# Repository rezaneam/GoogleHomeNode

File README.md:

# Smart IoT Sensor - Lite Version of [sAmbiente](https://github.com/rezaneam/sAmbiente)

This project introduces proof of concept for a Smart Home Device/Sensor/Monitoring with a different approach.
In this project, Bosch & TI environment sensors (BMP280, BME280, BME680, HDC1080) were utilized to monitor the temperature, humidity, pressure, and air quality.

## What is innovative in this project

- The configuration process of the Smart IoT Sensor is straightforward and you can update it at anytime.
- The Sensor pushes real-time readings via BluetoothLE to multiple connected devices.
- Against many available solutions, you don't need to open a port in your router/modem/firewall. That's really cumbersome and may be secuirty issues.
- You don't need to deal with DNS and static IP address. that's a real pain.
- You don't need to register on expensive and complicated services (Azure IoT Hub service has a free plan).
- You can customize the whole project with a little effort.

## Components

This project includes the following components

- ESP32 (Smart IoT Sensor):

It's the main IoT device which basically is an ESP32 module connected to an environment sensor. The module needs to connect to the Internet via WiFi and connect to Azure services. This project is written in `Platform IO` so it should take care of everything (external libraries) if you use `Platform IO`.
You should be able to connect to the device and configure it via BluetoothLE and at any time, you can update the sensor configuration without any need to reset it.
WiFi name, Password, Azure Connection string, Google Home, device location (for example, kitchen, living room) are configuration values needed to be set. Hopefully, UWP and Xamarin applications will help you to do it with any challenges.

- UWP Application:

This application is just for configuring the Google Home node. It's basically a `Windows 10` application and will show up in `Windows store` soon :)
By the way, you can run on Desktop, Windows Mobile, and `Windows IoT Core` (`Raspberry Pi`).

- ~~Xamarin Application~~: (not ready yet)

This project is an extended version of UWP Application for `Android` and `iOS` platform. Not ready yet.

- Azure:

This is an Azure Function app if you want to use your own `Azure service`. contact me if you can't follow me.

## How set it up

- Google Home Node

First thing first, You need to build the Google Home Node device and program it.
I would recommend you first test it with a very basic ESP32 evaluation board and a BMP280/BME280 breakout board. This setup would cost you less than 5 USD. Of course, having a `SSD1306` is a plus.
Wire the sensor as is shown in the following figure and flash the board via Platform IO in `Visual Studio Code`.

You can always reconfigure the connection by changing the pin numbers in [config.h](ESP32/src/config.h).

You can also use the PCB design to make your custom compact module with more functionality and battery support.
Find the attached 3.5x3.5 cm [PCB design](/KiCad-Design/KiCad-Design.kicad_pcb).

PCB layout

<span align="center">

</span>

- Azure IoT Hub

After creating the `Azure` account the first step is to make a new `IoT Hub` service in your Azure account. To do so just type in IoT Hub and create a new account (you pick F1 which is entirely free). Then Navigate to the IoT Hub service you created and make an IoT Device.
Click on the IoT Device that you have just created and copy the connection string. You need to set this connection string in your Google Home node.
To test if this part is working properly just send a direct method with the following payload and check the logs in your serial port.

{
"Action": "Google Home",
"UserID": "`YourUserID`",
"Language": "en",
"Key": "temperature"
}

So, now you are done with this part.

- Azure Function

In the same way make an `Azure Function App` service in your Azure account. Pick .Net 3.1 version and Free version in the Function App.
Open Azure project repository and update the _IoTHubName_, _IoTDeviceName_, and _IoTSharedAccessKey_ values and then Publish the function in your Azure account.
To test this step just copy the Function App **URL** and use postman to send a post message with the following body.

{
"Action": "Google Home",
"UserID": "`YourUserID`",
"Language": "en",
"Key": "temperature"
}

- IFTTT

You need to make an IFTTT account (it's free) and make a scenario called.
Try to create an applet in IFTTT, add `Google Assistant` as a trigger source. Remember to pick _say a phrase with a text ingredient_
Type in your preferred keywords followed by $ sign and provide a response for that.
Then pick `Webhooks` (web request) as the service. So copy and paste the `Azure Function App` URL from the previous step in URL field. You pick either Get or Post request and for the content type choose JSON. paste the following structure there.

{
"Action": "Google Home",
"Language": "en",
"UserID": "`YourUserID`",
"Key": "TextField"
}

## How it is working

The following figure shows the overal concept of the project.

The Google Home Node (main ESP32 module) starts to connect to Azure IoT service (as set in the configuration) and tries to find the local `Google Home speaker` (namely Google Home, Google Home Mini, or any Google Home enable speaker). It also drives the OLED and the sensor.
The Google Home Node is always in listening mode (at least for now) and doesn't send any information to `Azure IoT Hub`.

When you ask `Google Assistant` to give you the home temperature (or specific location/node), Google Assistant (not Google Home speaker) triggers an action in the IFTTT (which you have previously defined).

`IFTTT` triggers a webhook (better to an HTTP request) which actually an Azure Function with some inputs (username, keywords).
The received information from Azure Function is sent to the Azure IoT and eventually received by the Google Home Node.

Google Home Node would take action if the received information matches (username, location, etc.). So Google Home Node asks the Google Home speaker (already linked) to say the temperature, humidity, ... values.
I used [esp8266 Google TTS](https://github.com/horihiro/esp8266-google-tts) to generate an audio file and [esp8266 Google Home Notifier](https://github.com/horihiro/esp8266-google-home-notifier) to push the message/notification to the Google Home Speaker.

## Platform/IDE(s)

- [Platform IO](https://platformio.org/)
- [Arduino](https://www.arduino.cc/)
- [Espressif ESP-32](https://www.espressif.com/en/products/socs/esp32)

## Supported Sensors

- [Bosch BMP280](https://www.bosch-sensortec.com/products/environmental-sensors/pressure-sensors/bmp280/)
- [Bosch BME280](https://www.bosch-sensortec.com/products/environmental-sensors/humidity-sensors-bme280/)
- [Bosch BME680](https://www.bosch-sensortec.com/products/environmental-sensors/gas-sensors/bme680/). You need a [permission](https://www.bosch-sensortec.com/media/boschsensortec/downloads/bsec/2017-07-17_clickthrough_license_terms_environmentalib_sw_clean.pdf) to use [Bosch Sensortec Environmental Cluster(BSEC) Library](https://github.com/BoschSensortec/BSEC-Arduino-library). Please visit this [page](https://www.bosch-sensortec.com/software-tools/software/bsec/)
- [Texas Instrument HDC1080](https://www.ti.com/lit/ds/symlink/hdc1080.pdf)

## Dependent Libraries

- [Azure IoT Arduino](https://github.com/Azure/azure-iot-arduino)
- [Azure IoT Protocol HTTP](https://github.com/Azure/azure-iot-arduino-protocol-http)
- [Azure IoT Protocol MQTT](https://github.com/Azure/azure-iot-arduino-protocol-mqtt)
- [Azure IoT Utility](https://github.com/Azure/azure-iot-arduino-utility)
- [NimBLE Arduino](https://github.com/h2zero/NimBLE-Arduino) - Lite version of the BluetoothLE to save some RAM
- [esp8266 Google Home Notifier](https://github.com/horihiro/esp8266-google-home-notifier) - Customized version to support different languages.
- [esp8266 Google TTS](https://github.com/horihiro/esp8266-google-tts)
- [Adafruit BME280 Library](https://github.com/adafruit/Adafruit_BME280_Library) - Locally/Modified in the project
- [ThingPulse SSD1306](https://github.com/ThingPulse/esp8266-oled-ssd1306) - Extensively modified and locally imported.
- [BSEC Arduino Library](https://github.com/BoschSensortec/BSEC-Arduino-library) - Please visit this [page](https://www.bosch-sensortec.com/software-tools/software/bsec/)
- TO DO: [Texas Instrument HDC1080](https://www.ti.com/lit/ds/symlink/hdc1080.pdf)

## Future Improvment

- Improving the UWP Application layout and code logic
- Deploy UWP App in the Windows Store
- Support for Android & iOS platforms (Xamarin Forms)
- Better desgin for multi-language support (EN, DE, FR)
- Find a way to integrate with Google Assistant
- Connect to [HASS](https://www.home-assistant.io/)

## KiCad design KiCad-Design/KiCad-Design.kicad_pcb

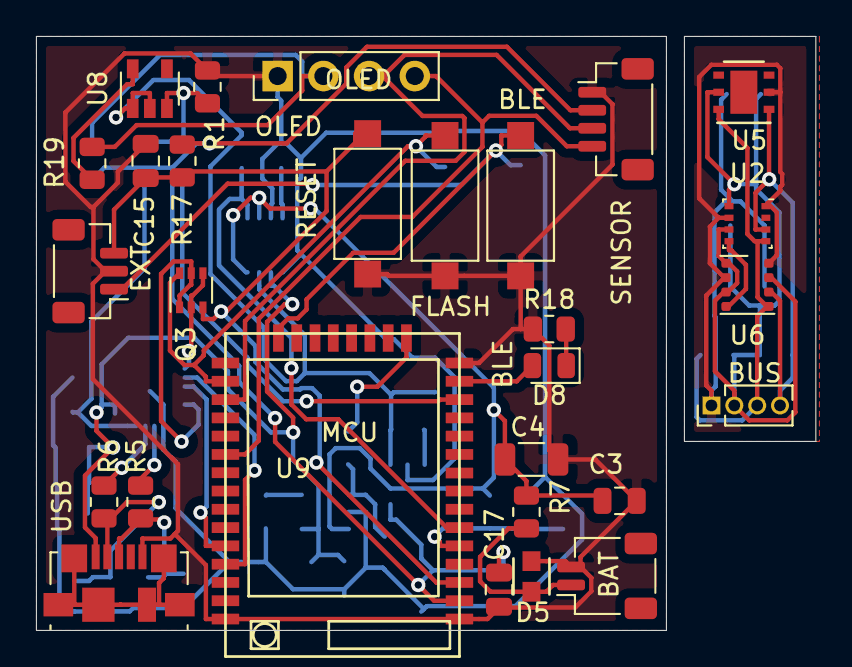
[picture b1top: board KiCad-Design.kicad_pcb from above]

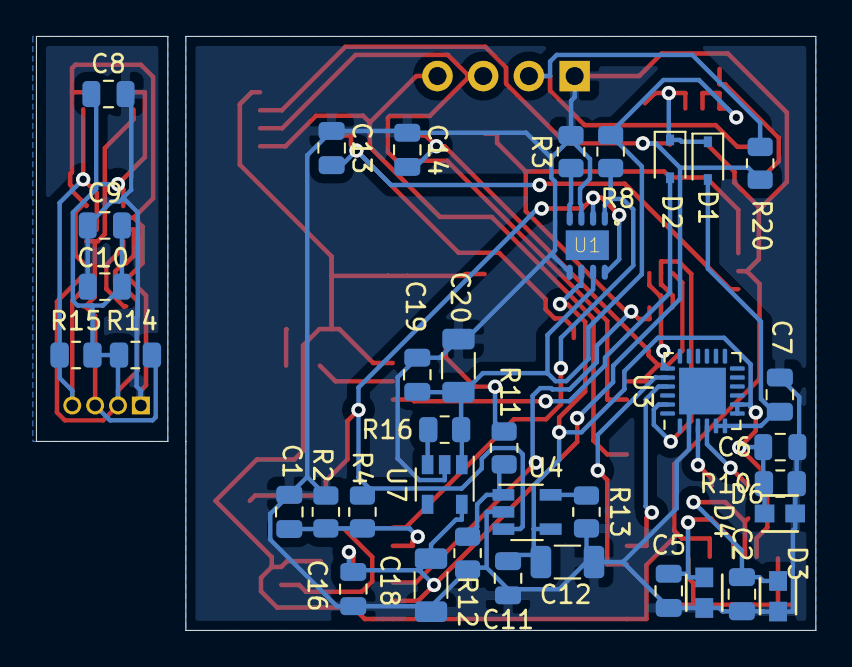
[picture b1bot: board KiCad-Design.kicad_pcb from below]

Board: 2 copper layers, 43.3 x 33.0 mm, 65 parts (37 on the bottom side), 38 nets.

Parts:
BAT: Battery; JST_SH_SM02B-SRSS-TB_1x02-1MP_P1.00mm_Horizontal
BLE: MCU BLE Adv; SW_SPST_CK_RS282G05A3
BUS: SENSOR; PinHeader_1x04_P1.27mm_Vertical
C1, C16: 10pF; C_0805_2012Metric
C2, C5: 47pF; C_0805_2012Metric
C3, C7, C8, C9, C10, C11, C13, C14, C15, C17, C19: 100nF; C_0805_2012Metric
C4, C12: 10uF; C_1206_3216Metric
C6: 100pF; C_0805_2012Metric
C18, C20: 100uF; C_1206_3216Metric
D1, D2: 1N4148WS; D_SOD-323
D3, D4, D5, D6: 0603ESDA2-TR2; Eaton-0603ESDA-0-0-0
D8: LED; LED_0805_2012Metric
EXT: Ext; JST_SH_BM03B-SRSS-TB_1x03-1MP_P1.00mm_Vertical
FLASH: MCU FLASH; SW_SPST_CK_RS282G05A3
J1: USB_B_Micro; USB_Micro-B_Molex_47346-0001
OLED: OLED; PinHeader_1x04_P2.54mm_Vertical
Q3: UMH3N; SOT-363_SC-70-6
R1, R12: 33K; R_0805_2012Metric
R2, R4, R10, R16, R17: 100K; R_0805_2012Metric
R3: 1K; R_0805_2012Metric
R5, R6, R18: 33R; R_0805_2012Metric
R7: 0R; R_0805_2012Metric
R8, R11: 10K; R_0805_2012Metric
R13: 2K; R_0805_2012Metric
R14, R15: 4.7K; R_0805_2012Metric
R19, R20: 0K; R_0805_2012Metric
RESET: MCU RESET; SW_SPST_CK_RS282G05A3
SENSOR: SENSORS; JST_SH_BM04B-SRSS-TB_1x04-1MP_P1.00mm_Vertical
U1: TPS2115A; SON-8
U2: BME280; Bosch_LGA-8_2.5x2.5mm_P0.65mm_ClockwisePinNumbering
U3: CP2104; QFN-24-1EP_4x4mm_P0.5mm_EP2.6x2.6mm
U4: LTC4054ES5-4.2; TSOT-23-5
U5: HDC1080; Texas_PWSON-N6
U6: BME680; Bosch_LGA-8_3x3mm_P0.8mm_ClockwisePinNumbering
U7, U8: AP2112K-3.3; SOT-23-5
U9: ttgo-32-micro; TTGO-32-MICRO

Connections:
+3.3VA: R19.2, U8.5
+3V3: C16.2, C17.2, C18.1, R17.2, R20.2, SENSOR.2, U7.5, U9.2
+5V: C6.2, C11.1, C12.1, D6.1, J1.1, R10.2, U1.6, U3.7, U3.8, U4.4
+BATT: C3.2, C4.1, R4.2, R7.2, U1.2, U1.8, U4.3
+VSW: C7.2, D1.2, U3.5, U3.6
GND: BAT.2, BLE.2, C1.2, C2.1, C3.1, C4.2, C5.1, C6.1, C7.1, C11.2, C12.2, C13.1, C14.1, C15.1, C16.1, C17.1, C18.2, C19.1, C20.2, D3.2, D4.2, D5.2, D6.2, EXT.2, FLASH.2, J1.5, OLED.1, R1.2, R2.2, R3.2, R10.1, R12.1, R13.1, R18.1, RESET.2, SENSOR.1, U1.3, U1.5, U3.2, U3.25, U4.2, U7.2, U9.1, U9.15, U9.38
MCU_BAT_REF: C1.1, R2.1, R4.1, U9.5
MCU_BLE_Adv: BLE.1, C13.2, EXT.1, U9.23
MCU_CHARGING: R11.2, U9.16
MCU_EN: D2.2, U9.13
MCU_FLASH: C14.2, FLASH.1, Q3.6, U9.25
MCU_LED: D8.2, U9.14
MCU_POWER_MODE: R8.1, U1.1, U9.6
MCU_RESET: C15.2, EXT.3, Q3.3, R17.1, RESET.1, U9.3
MCU_RX: U3.21, U9.34
MCU_SCL: OLED.3, SENSOR.3, U9.26
MCU_SDA: OLED.4, SENSOR.4, U9.29
MCU_TX: U3.20, U9.35
unnamed: C2.2, D3.1, J1.2, R6.1
unnamed: C5.2, D4.1, J1.3, R5.1
unnamed: D1.1, D2.1, R1.1, U8.3
unnamed: BAT.1, D5.1, R7.1
unnamed: D8.1, R18.2
unnamed: OLED.2, R19.1, R20.1
unnamed: Q3.1, Q3.5, U3.23
unnamed: Q3.2, Q3.4, U3.19
unnamed: R3.1, U1.4
unnamed: R11.1, R12.2, U4.1
unnamed: R13.2, U4.5
unnamed: R16.1, U7.3
SEN_GND: BUS.1, C8.2, C9.2, C10.2, U2.1, U2.7, U5.2, U6.1, U6.7
SEN_SCL: BUS.3, R15.1, U2.4, U5.6, U6.4
SEN_SDA: BUS.4, R14.1, U2.3, U5.1, U6.3
SEN_VCC: BUS.2, C8.1, C9.1, C10.1, R14.2, R15.2, U2.6, U2.8, U5.5, U6.2, U6.6, U6.8
Sensor_add: U2.5, U6.5
USB_D+: R5.2, U3.3
USB_D-: R6.2, U3.4
VCC: C19.2, C20.1, R8.2, R16.2, U1.7, U7.1, U8.1, U8.2

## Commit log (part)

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2020-12-25 * Adding ESP32 project in platformio * Configuring the project * Adding the basic functionality * Adding basic BLE GATT * Adding basic WiFi
2020-12-25 * Adding to do plans
2020-12-25 Adding support for external button triggered BLE Adding extension for showing BLE and WiFi status on OLEd
2020-12-28 Adding missing event change
2020-12-28 Updating the to do list
2020-12-28 Adding the basic support for reading values from BME280
2020-12-28 * Adding BLE descriptors for notifying values * Updating the sensor values in the BLE stack
2020-12-29 * Adding support for Flash memory storage for saving wifi and google home information
2021-01-02 * Removing redundant serial prints * Switching to NimBLE library
2021-01-02 * Adding basic support for the google home notify
2021-01-02 * Adding the missing code for monitoring the changes done by the user. (onWrite) * Fixing the notify trigger by checking the characteristics is notifiable
2021-01-02 * Adding Google Home basic profile to GATT
2021-01-03 Improving OLED library
2021-01-03 Moving BME280 library
2021-01-03 Adding basic UWP project for BLE configure tool
2021-01-03 UWP: Adding basics of the Config Tool - Google Home Node * Adding search and connect to device (deviceWatcher) * Adding google node class (services, characteristics, descriptors) * Adding subscribers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
2021-01-03 Adding Cloud icon
2021-01-05 Clean up - main.cpp
2021-01-05 * Fixing protocol error issue for wireless password * improving the logic for setting SSID & Password and connecting to WiFi
2021-01-05 Adding Restart and Factory Rest feature
2021-01-05 Adding factory reset uuid description.
2021-01-22 Clean-up
2021-01-25 Fixing WiFi connection lock
2021-01-26 Basics of Azure IoT
2021-01-28 IoT Azure Hub Basics 2
2021-01-28 Adding support for cloud and air quality icons
2021-01-28 Adding BMP280 support
2021-01-28 Fixing WiFi lock issue when scanning the networks after failed connection.
2021-01-29 Adding support for string connection of Azure IoT Hub in BLE GATT and EEPROM
2021-01-29 Fixing the sensor measurements digits for BME680
2021-01-29 Adding Reset/Restart support for UWP project
2021-01-30 Improving the event routing
2021-01-30 Adding the basic support for handling Azure messages * temperature & humidity
2021-01-30 Adding Support for Device location & Securing the Azure Connection string
2021-01-30 Adding the basic support for setting (1) google home name, (2) azure connections string, (3) device location
2021-01-30 Adding the missing enums.h and removing the redundant files.
2021-01-31 Using connection status characteristics for exposing the connection status of WiFi, Google Home and Azure IoT Hub
2021-02-01 Adding event Queue scheduler
2021-02-01 Adding azure class to move the relevant logic outside of the main.cpp
2021-02-01 Removing Azure IoT Hub stuffs from main.cpp and use the class instead.
2021-02-01 Fixing the missing definition
2021-02-02 Moving WiFi stuff to a class.
2021-02-02 Moving Google Home stuff into a library
2021-02-03 Fixing BLE advertise timeout logic Correct the Azure connection events improving OLED logic improving the event handling the in main.cpp abstracting the frequent update status tasks
2021-02-03 Adding the missing google home status update
2021-02-03 Moving the BLE stuff to a class
2021-02-04 Adding missing stuff after moving BLE to a class
2021-02-04 Old BLE code cleanup. It is safe to move
2021-02-04 Fixing WiFi search issue in UWP project
2021-02-05 BLE library clean up
2021-02-05 * Use connection string stored in the flash * Adding verbose flag for printing outputs
2021-02-05 Code cleanup
2021-02-05 Code clean up + planning for future improvements
2021-02-09 Adding support for device location and username in the Flash
2021-02-09 Adding events for username & device location
2021-02-09 Adding support for userId to process the received messaged from AzureIoT
2021-02-10 Fixing the naming of Storage Hub
2021-02-10 Adding the basic support for BME680
2021-02-11 First attempt to use BSEC library
2021-02-11 Adding support for UserID and Node Location
2021-02-12 Fixing the BLE Characteristics Initialization
2021-02-13 UWP App: Improving the view + support for the device disconnect
2021-02-13 UWP App : Adding missing pages
2021-02-13 UWP App : Adding support for disconnect and disposing the BLE object
2021-02-13 UWP App : Adding the basic support for the sensor values
2021-02-13 UWP App : Removing the old MainPage design
2021-02-28 Adding the basic ReadMe file
2021-03-02 PCB : Small update on the PCB design
2021-03-03 PCB : Initial PCB Design
2021-03-03 PCB : Adding Missing files
2021-03-03 ESP32 : Initial organizing the notifier
2021-03-03 PCB : Finalizing the PCB v1
2021-03-03 Assets : Adding Documentation Materials
2021-03-03 Documentation : Giving some information about the project
2021-03-03 Documentation : more information about the project ;)
2021-03-03 Documentation : More detail about the project
2021-03-03 Documenation : Fixing the formats
2021-03-03 Documentation : Adding License file. MIT enjoy it ;)
2021-03-04 Documentation : more information content
2021-03-04 PCB : Adjusting the labels on the PCB file
2021-03-04 Document : Adding PCB images in the README.md
2021-03-05 PCB : Removing the redundant files
2021-03-06 ESP32 : Adding initial support for daily summary of measurements
2021-03-06 ESP32 : changing a dependency to something that allows us to modify the language
2021-03-07 ESP32 : Adding initial multi-language support
2021-03-07 ESP32 : Adding support for Summary keyword
2021-03-07 Updating the ReadMe.file
2021-03-07 Document : Updating the Diagram.png
2021-03-07 Documentation ; Updating the Image Frame
2021-03-07 ESP32 : Basic Support for Dual language
2021-03-09 ESP32 : Downgrading espressif32 v3.0.0 - due to introduced bug in v3.1.0
2021-03-09 ESP32 : Introducing the basic temperature summary report
2021-03-09 ESP32 : Adding support for handling temperature summary
2021-03-09 ESP32 : Fixing sensor values
2021-03-09 ESP32 : Fixing sensor's initial value (for pressure didn't work the last one)
2021-03-09 ESP32 : Adding WiFi log
2021-03-09 ESP32 : Fixing the initial value overflow issue
2021-03-09 ESP32 : Adding rotary logic for displaying sensor measurements
2021-03-10 ESP32 : Adding better Fonts
2021-03-10 ESP32 : Fixing Display loop issue when using air quality sensor + checking the wifi connectivity before try to connect to the cloud
2021-03-10 ESP32 : Moving unused methods to private section
2021-03-10 Fixing the grammar mistakes
2021-03-11 ESP32 : Adding BLE LED blink when advertising
2021-03-11 ESP32: Showing time in the rotary display
2021-03-11 Azure : Updating the Azure Function to support multi-language
2021-03-11 Azure : Removing the redundant code
2021-03-12 ESP32 : Fixing the WiFi connection failed bug
2021-03-12 Azure : Fixing the IoTHubName
2021-03-12 UWP : Fixing the search field
2021-03-13 providing more information about the setup.
2021-03-13 Documentation : Adding more setup information
2021-03-13 UWP : Updating the app manifest
2021-03-13 Documentation : Changing the project Name
2021-03-14 ESP32 : Adding support for average value
2021-03-14 ESP32 : Fixing the precision issue with the average value
2021-03-14 ESP32 : Full support for average value
2021-03-14 ESP32 : forgot to evaluate the isWificonnected flag before fetching the time.
2021-03-15 ESP32 : Adding New Font size for displaying the Date without crop
2021-03-15 PCB : Adding HDC1080 in the design
2021-03-15 PCB : Adding the step file for HDC1080
2021-03-15 ESP32 : Making the external sensors TwoWire bus configurable
2021-03-15 ESP32 : Fixing the temperature subtraction error
2021-03-15 ESP32 : Support for multi-bus/interface OLED-Sensors * Fixing the local time reading error * Updating the measurement values in BLE characteristics
2021-03-15 PCB : Using UMH3N package instead of PMBT3904
2021-03-15 ESP32 : Updating the Summary report
2021-03-15 ESP32 : moving the general configuration in the separate header file
2021-03-17 Documentation : Updating the diagram
2021-03-17 Documentation : Using the connections
2021-03-17 PCB : detaching the sensors from the main PCB
2021-03-17 PCB : Updating the Schematic design
2021-03-17 PCB : Including the missing 3D step files
2021-03-17 PCB: Updating the PCB design file :)
2021-03-17 Documentation : Updating the assets
2021-03-17 Documentation : Updating the images
2021-03-17 Documentation : Updating the ReadMe file
2021-03-18 ESP32 : Adding French support
2021-03-18 ESP32 : Adding Notifying Icons when Pushing Audio to Google Home Speaker
2021-03-19 ESP32 : Code improving
    * Fixing the bug with different I2C bus
    * improving the sensor type management
    * First attempt to use BSEC library
    * Fixing the measurements log print mistake
2021-03-21 ESP32 : Fixing the sensor identification bug
2021-03-22 ESP32 : Improving the show messages
2021-03-22 ESP32 : Fixing the Air Quality min/max/ave measurements
2021-03-22 ESP32 : Monitoring the sensor calibration status
2021-03-22 ESP32 : Adding Support for extended OLED display + BME680 calibration status
2021-03-22 ESP32 : Adding the missing definition
2021-03-22 ESP32 : Support for monitoring the status
2021-03-22 Documentation : Updating the documentation BME680 support
2021-03-22 ESP32 : Fixing the bug with the storing the average
2021-03-22 ESP32 : Auto restart when heap size is too-low (Azure IoT issues)
2021-03-23 ESP32 : Accepting the Medium Accuracy for BME680
2021-03-23 ESP32 : Showing the L/M for Low and MEDIUM_ACCURACY
2021-03-24 ESP32 : Adding support for storing BSEC state in the Flash
2021-03-24 ESP32 : Fixing the introduce bug
2021-03-24 ESP32 : Fixing the daily report reset (with this it will reset the report everyday at 6am or every 1440 minutes)
2021-03-24 ESP32: resolving the local time using worldtimeapi.org api
2021-03-24 ESP32 : setting BSEC config for BME680
2021-03-25 ESP32 : Adding support for Air Quality Index in the BluetoothLE GATT
2021-03-25 ESP32 : Passing the Air Quality Index Value
2021-03-25 ESP32 : Showing the Summary of Air Quality
2021-03-25 ESP32 : Fixing the bug with Flash memory address
2021-03-25 ESP32 : Adding ping feature for checking the connection
2021-03-25 ESP32 : Updating the UWP project to support the Air Quality and improve the visuals
2021-03-26 ESP32 : Small clean up
2021-03-27 ESP32 : Showing equivalent VOC in the display + improving the description for the AQI
2021-03-27 ESP32 : Adding verbose mode support for Sensor wrapper
2021-03-28 ESP32: Fixing the missing verbose mode flag for sensor wrapper
2021-03-29 ESP32 : Adding the Internet connenction Icon
2021-03-29 ESP32: Adding support for VOC based warning
2021-03-29 ESP32: Including daylight saving time into account
2021-03-29 ESP32 : Fixing the VOC scale
2021-03-30 UWP: Updating the AOI in the sensor monitoring section + setting 19041 as target version
2021-04-02 MISC: Committing some left overs
2021-04-03 ESP32: Printing the CO2 values as well
2021-04-03 PCB: Moving the ESP32 Library to a folder
2021-04-03 PCB: Moving the libraries to the project specific
2021-04-03 Xamarin: Initial project
2021-04-05 ESP32: Supporting de-initializing the IoT object
2021-04-05 ESP32: Support Disconnect WiFi
2021-04-06 ESP32: Disconnect WiFi if fails to ping the gateway + stop Azure if the internet is not available
2021-04-06 Xamarin: Granting permissions for BLE
2021-04-07 ESP32: Support auto reconnect in Wireless library
2021-04-07 ESP32: Minor things with Google Home + introducing new events
2021-04-07 MCU: Introducing auto-reconnect. Known issue Azure Destroy
2021-04-07 UWP: Checking whether the Bluetooth module exist and turned on before scanning
2021-04-08 ESP32: Adding support for HDC1080
2021-04-08 ESP32: Adding the missing changes
2021-04-09 PCB: Updating TTGO library
2021-04-11 PCB: Adding TPS2115A library
2021-04-11 PCB: Re-validating the Schematic design
2021-04-11 PCB : Updating the Schematic PDF file
2021-04-12 PCB: Updating PCB layout
2021-04-17 ESP32: Fixing the memory release + upgrading to latest espressif32 library
2021-04-20 ESP32: Some little memory improvement
2021-04-23 Update README.md
    Organizing the projects
2021-05-12 ESP32: Some leftovers from the other branch
2021-07-04 MCU: Adding support for pushing a plain text via COMMAND keyboard
2021-07-29 PCB: Adding the kicad table
